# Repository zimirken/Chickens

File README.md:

# Chickens
Various automation projects for the chicken coop.

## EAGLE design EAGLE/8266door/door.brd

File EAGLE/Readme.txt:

This contains my custom eagle libraries that I used to make this. Also the eagle files for these boards.

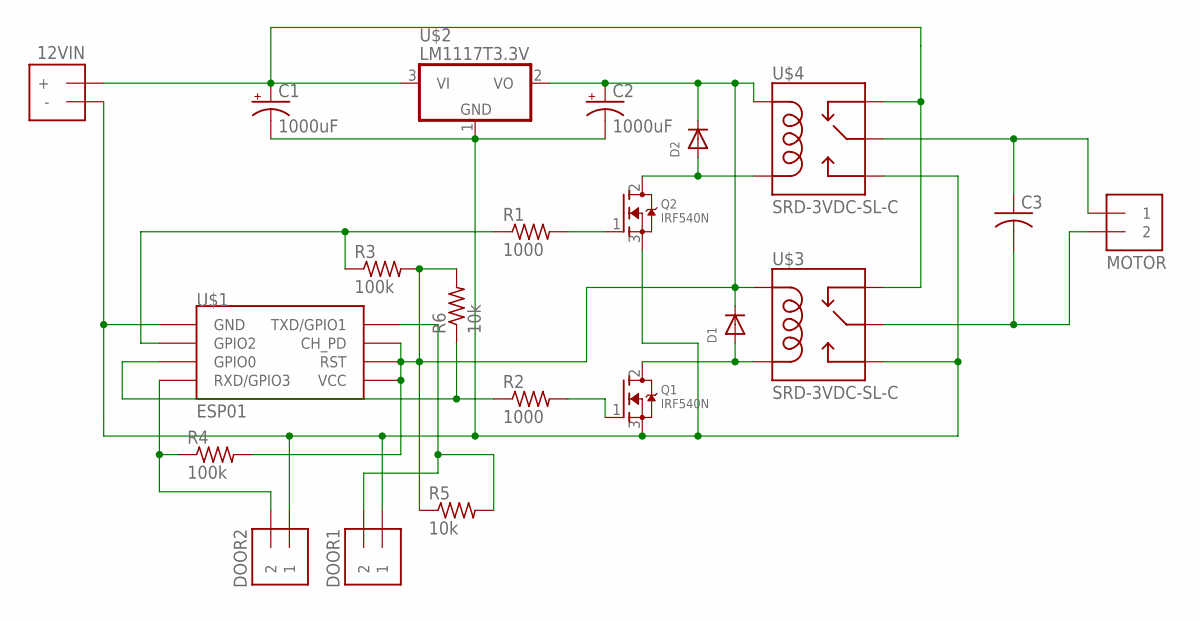
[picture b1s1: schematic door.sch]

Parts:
12VIN: 1X2_-++-; 1X2_+-
C1, C2: 1000uF; E5-10,5
C3: C-US150-054X183; C150-054X183
D1, D2: DIODEDO-1N4148; DO-1N4148
DOOR1, DOOR2: 1X2_1212; 1X2_12
MOTOR: 1X2_1221; 1X2_21
Q1, Q2: IRF540N; TO220V
R1, R2: 1000; 0207/12
R3: 100k; 0204/7
R4: 100k; 0207/12
R5, R6: 10k; 0204/7
U$1: ESP01
U$2: LM1117T3.3V; TO220V
U$3, U$4: SRD-3VDC-SL-C; SRD-05VDC-SL-C

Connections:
unnamed: C2.+, D1.C, D2.C, R3.2, R4.2, R5.1, R6.2, U$1.CH_PD, U$1.RST, U$1.VCC, U$2.2 (VO), U$3.COIL1, U$4.COIL1
unnamed: D2.A, Q2.2 (D), U$4.COIL0
unnamed: D1.A, Q1.2 (D), U$3.COIL0
unnamed: 12VIN.+, C1.+, U$2.3 (VI), U$3.SWCLOSED (SWCLOSE), U$4.SWCLOSED (SWCLOSE)
unnamed: 12VIN.-, C1.-, C2.-, DOOR1.1, DOOR2.1, Q1.3 (S), Q2.3 (S), U$1.GND, U$2.1 (GND), U$3.SWOPEN, U$4.SWOPEN
unnamed: C3.1, MOTOR.1, U$4.SWCOMMON
unnamed: C3.2, MOTOR.2, U$3.SWCOMMON
unnamed: Q1.1 (G), R2.2
unnamed: Q2.1 (G), R1.2
unnamed: R1.1, R3.1, U$1.GPIO2
unnamed: R2.1, R6.1, U$1.GPIO0
unnamed: DOOR2.2, R4.1, U$1.RX (RXD/GPIO3)
unnamed: DOOR1.2, R5.2, U$1.TX (TXD/GPIO1)

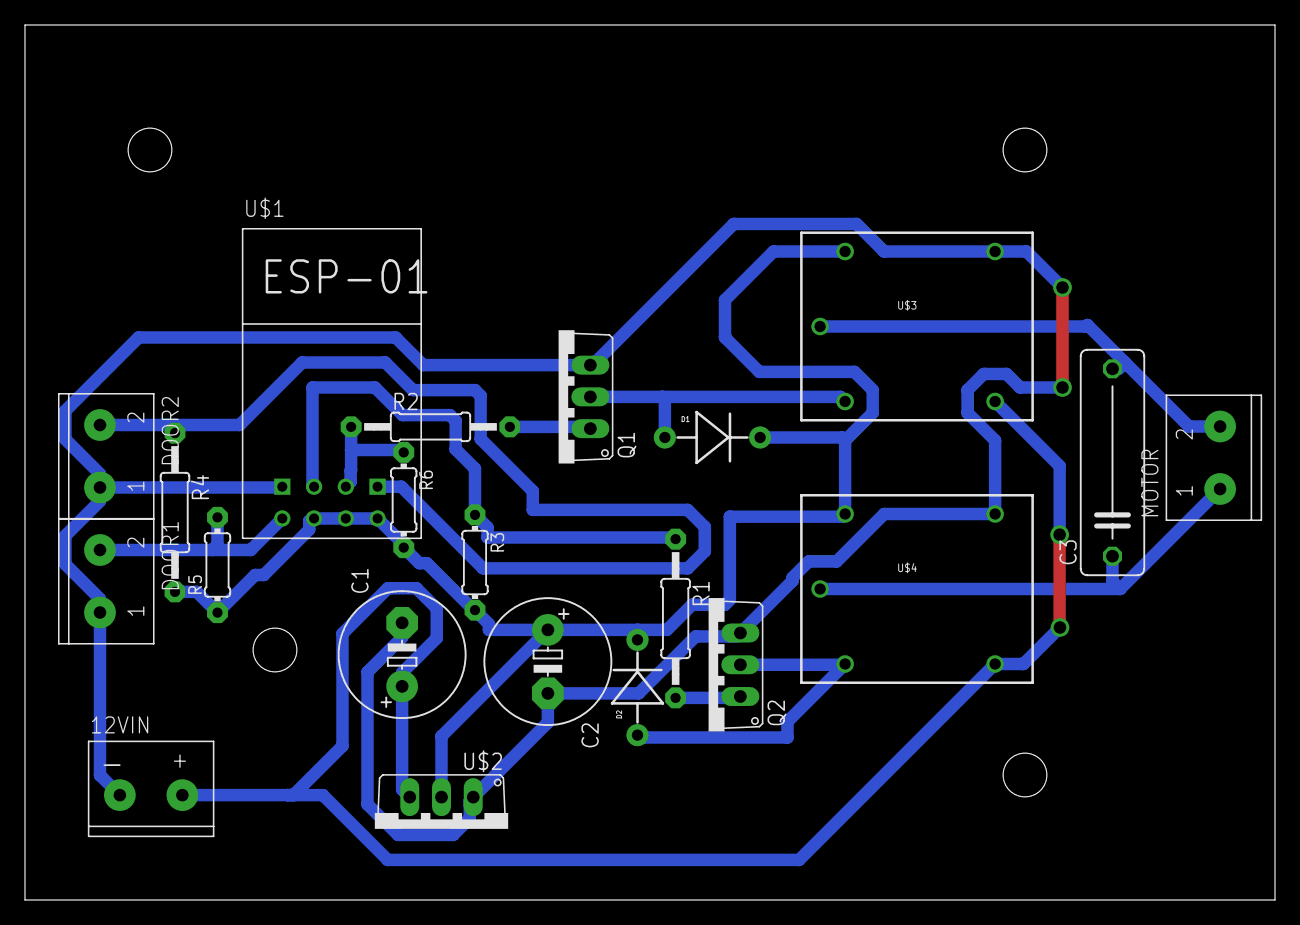
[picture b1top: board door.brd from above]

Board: 2 copper layers, 100.0 x 70.0 mm, 21 parts (0 on the bottom side), 13 nets.

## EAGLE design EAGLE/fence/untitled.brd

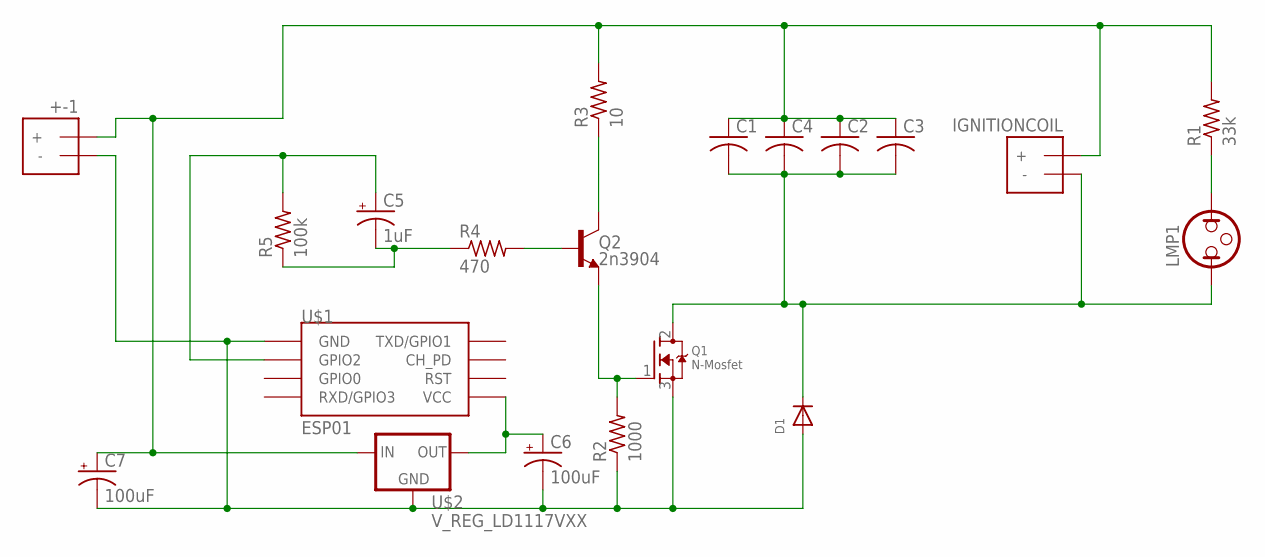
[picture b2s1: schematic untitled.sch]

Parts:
+-1: 1X2_-++-; 1X2_+-
C1, C2, C3, C4: C-US225-062X268; C225-062X268
C5: 1uF; E2-5
C6, C7: 100uF; E2,5-6
D1: DIODEDO-1N4148; DO-1N4148
IGNITIONCOIL: 1X2_-++-; 1X2_+-
LMP1: NEON; LDH-3R
Q1: N-Mosfet; TO220V
Q2: 2n3904; TO-92INSERT
R1: 33k; 0204/7
R2: 1000; 0204/7
R3: 10; 0204/7
R4: 470; 0204/7
R5: 100k; 0204/7
U$1: ESP01
U$2: V_REG_LD1117VXX; 78XXL

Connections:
unnamed: Q2.2 (B), R4.2
unnamed: C5.-, R4.1, R5.1
unnamed: +-1.-, C6.-, C7.-, D1.A, Q1.3 (S), R2.1, U$1.GND, U$2.IN (GND)
unnamed: LMP1.2, R1.1
unnamed: Q2.1 (C), R3.1
unnamed: Q1.1 (G), Q2.3 (E), R2.2
unnamed: +-1.+, C1.1, C2.1, C3.1, C4.1, C7.+, IGNITIONCOIL.+, R1.2, R3.2, U$2.OUT (IN)
unnamed: C1.2, C2.2, C3.2, C4.2, D1.C, IGNITIONCOIL.-, LMP1.1, Q1.2 (D)
unnamed: C5.+, R5.2, U$1.GPIO2
unnamed: C6.+, U$1.VCC, U$2.GND (OUT)

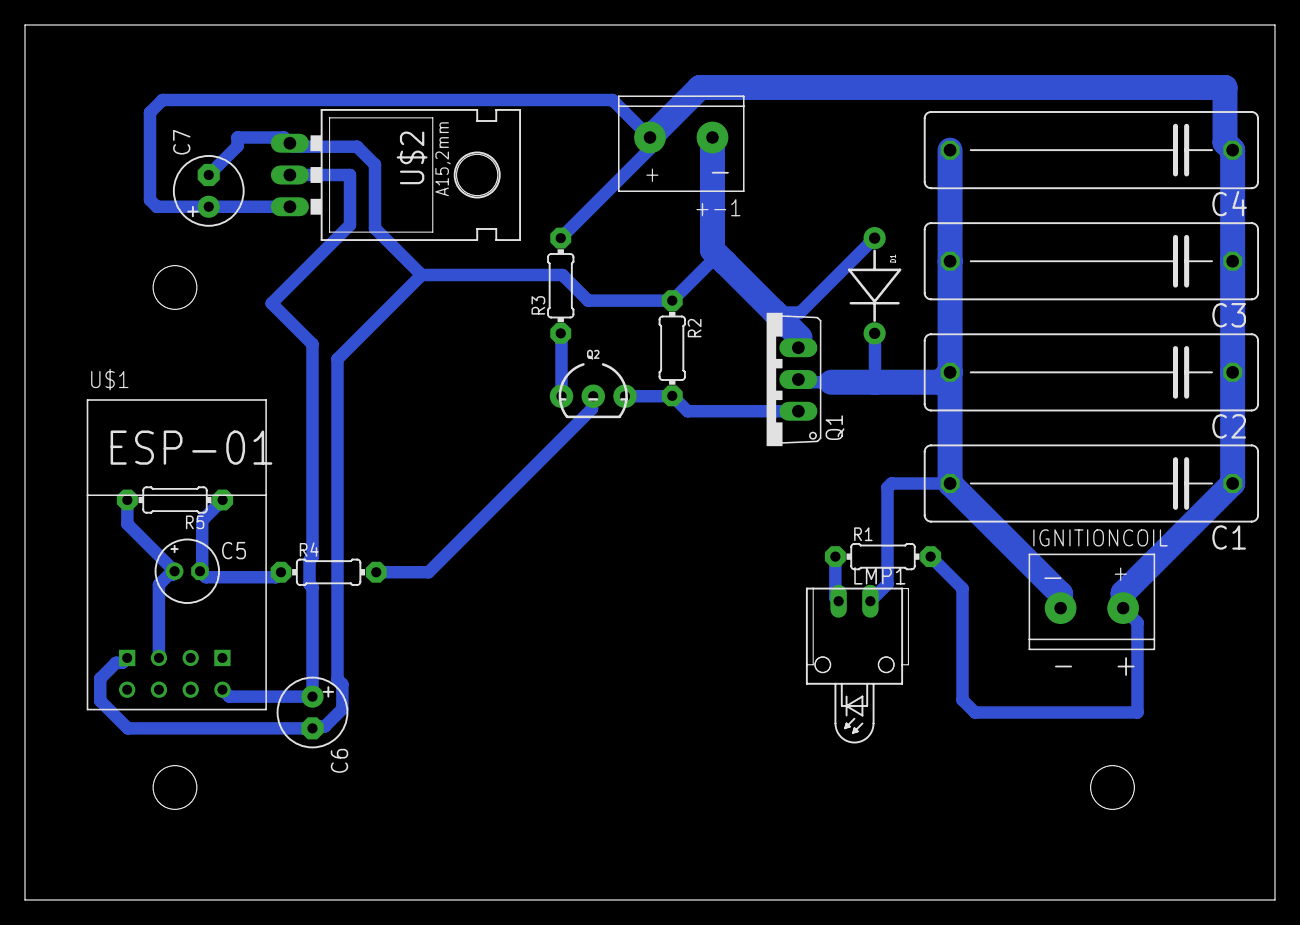
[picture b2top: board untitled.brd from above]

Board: 2 copper layers, 100.0 x 70.0 mm, 20 parts (0 on the bottom side), 10 nets.

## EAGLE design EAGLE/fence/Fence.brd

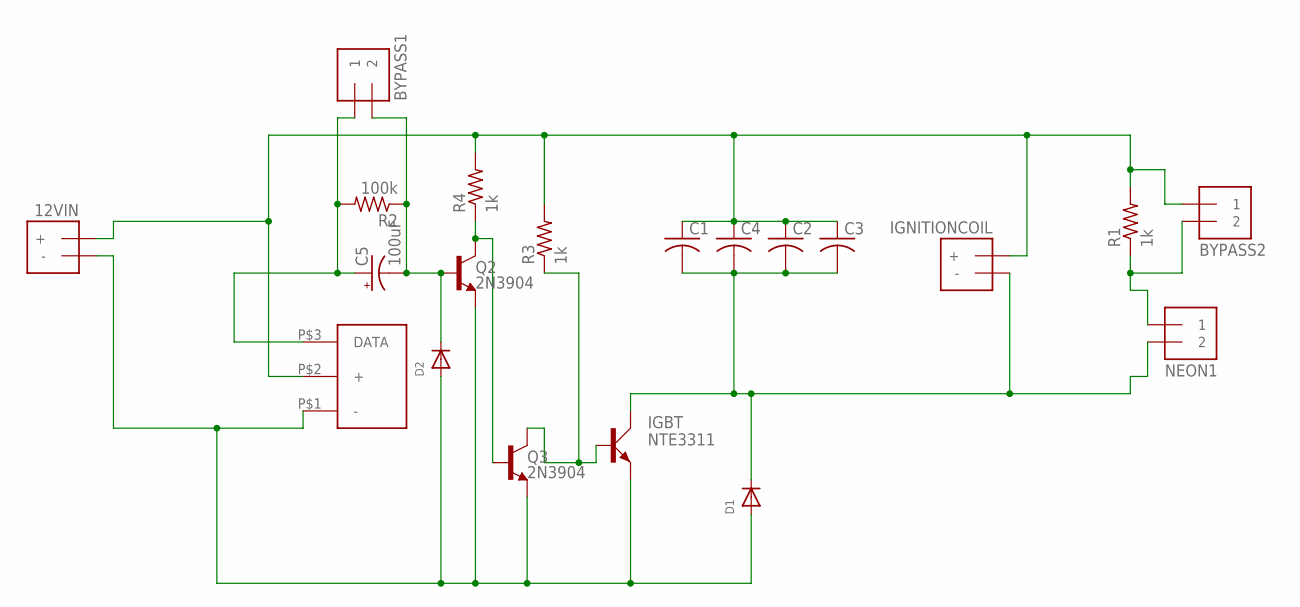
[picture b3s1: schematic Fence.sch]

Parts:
12VIN: 1X2_-++-; 1X2_+-
BYPASS1, BYPASS2: 1X2_12PINS; 1X2PINS
C1, C2, C3, C4: C-US225-062X268; C225-062X268
C5: 100uF; E2,5-5
D1, D2: DIODEDO-1N4148; DO-1N4148
IGBT: NTE3311; TOP3AV
IGNITIONCOIL: 1X2_-++-; 1X2_+-
NEON1: Neon Lamp; 1X2_12
Q2, Q3: 2N3904; TO-92INSERT
R1: 1k; 0204/7
R2: 100k; 0207/10
R3, R4: 1k; 0207/12
U$1: SERVO; 1X3

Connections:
unnamed: Q2.1 (C), Q3.2 (B), R4.1
unnamed: BYPASS1.2, C5.-, D2.C, Q2.2 (B), R2.1
unnamed: 12VIN.-, D1.A, D2.A, IGBT.E, Q2.3 (E), Q3.3 (E), U$1.P$1 (-)
unnamed: BYPASS2.2, NEON1.1, R1.1
unnamed: 12VIN.+, BYPASS2.1, C1.1, C2.1, C3.1, C4.1, IGNITIONCOIL.+, R1.2, R3.2, R4.2, U$1.P$2 (+)
unnamed: C1.2, C2.2, C3.2, C4.2, D1.C, IGBT.C, IGNITIONCOIL.-, NEON1.2
unnamed: IGBT.B, Q3.1 (C), R3.1
unnamed: BYPASS1.1, C5.+, R2.2, U$1.P$3 (DATA)

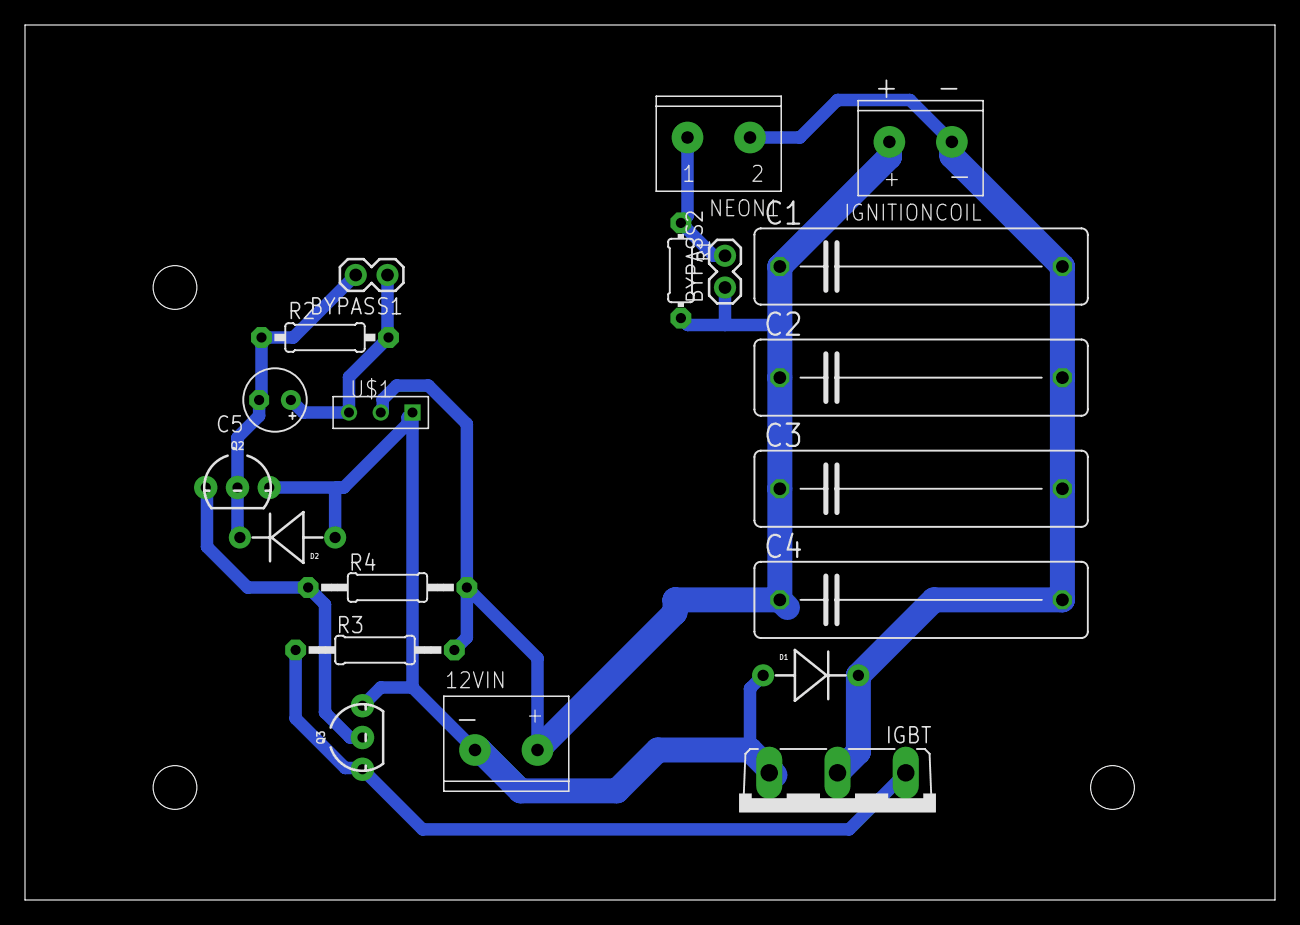
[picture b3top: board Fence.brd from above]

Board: 2 copper layers, 100.0 x 70.0 mm, 20 parts (0 on the bottom side), 8 nets.

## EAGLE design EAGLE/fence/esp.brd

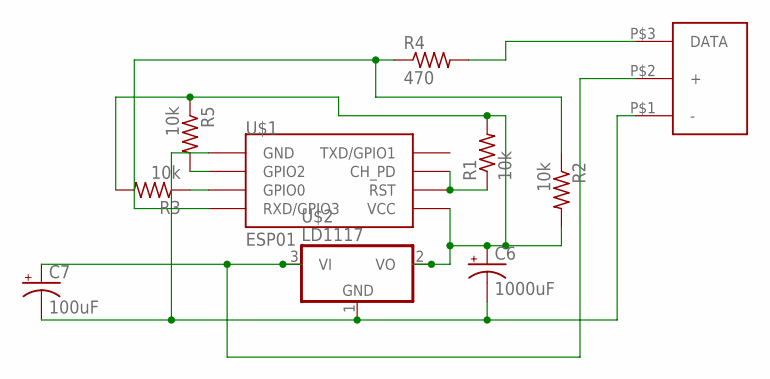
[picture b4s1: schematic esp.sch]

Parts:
C6: 1000uF; E5-10,5
C7: 100uF; E2,5-6
R1, R2, R3, R5: 10k; 0204/7
R4: 470; 0204/7
U$1: ESP01
U$2: LD1117; TO220V
U$3: SERVO; 1X3

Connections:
unnamed: R4.2, U$3.P$3 (DATA)
unnamed: R3.1, U$1.GPIO0
unnamed: C6.-, C7.-, U$1.GND, U$2.1 (GND), U$3.P$1 (-)
unnamed: R1.1, U$1.CH_PD, U$1.RST
unnamed: C6.+, R1.2, R2.2, R3.2, R5.1, U$1.VCC, U$2.2 (VO)
unnamed: R5.2, U$1.GPIO2
unnamed: R2.1, R4.1, U$1.RX (RXD/GPIO3)
unnamed: C7.+, U$2.3 (VI), U$3.P$2 (+)

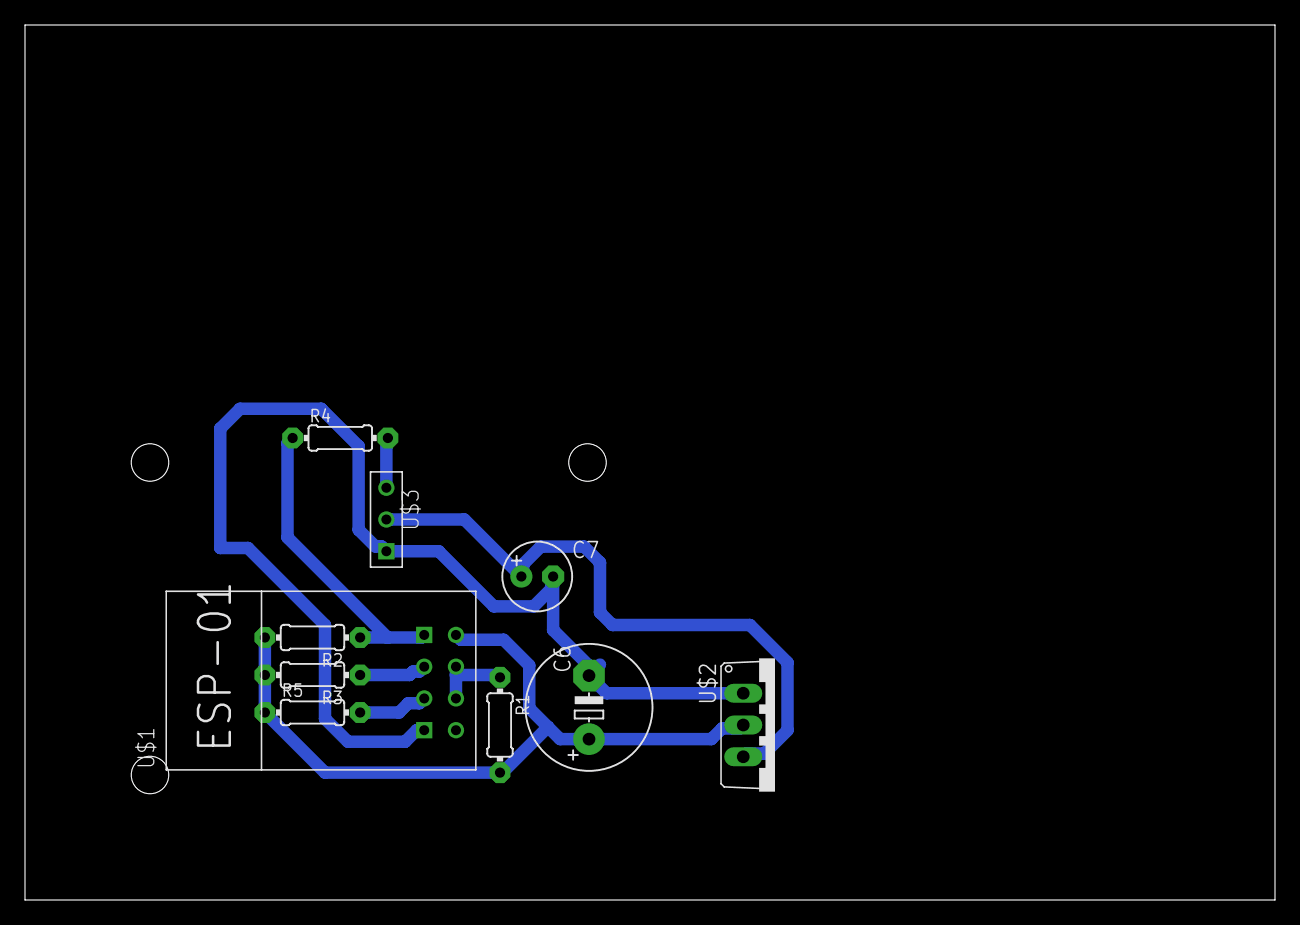
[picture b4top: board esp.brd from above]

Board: 2 copper layers, 100.0 x 70.0 mm, 10 parts (0 on the bottom side), 8 nets.

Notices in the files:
parts and their libraries:
SparkFun-DiscreteSemi: Licensing: Creative Commons ShareAlike 4.0 International - https://creativecommons.org/licenses/by-sa/4.0
